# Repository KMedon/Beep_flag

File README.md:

# Football Referee Flags with LoRa Communication
# Overview
This repository houses my engineering project, a cutting-edge set of football referee flags designed with LoRa technology for seamless and effective wireless communication. Aimed at transforming the communication dynamics for referees, especially in lower leagues where advanced communication tools may not be readily available, this project seeks to enhance decision-making accuracy and efficiency on the field.

# Genesis
The inspiration behind this project was to bridge the communication gap faced by referees in lower-tier football leagues. These leagues often lack the resources for sophisticated communication devices, impacting the referees' ability to make quick and accurate decisions. By developing a reliable and easy-to-use set of referee flags with a receiver, this project aims to provide a cost-effective solution that elevates the quality of game officiating across all levels of play.

# Technology
Utilizing LoRa (Long Range) technology at the 868 MHz frequency enables dependable wireless communication over considerable distances. The core of this system is the RAK3172 module, powered by an STM32WLE5 microcontroller, chosen for its performance and reliability. The project was developed in STM32CubeIDE, incorporating the Sub-GHz PHY library for managing wireless communications efficiently.

# Mechanical Design and Testing
The project extends beyond software and communication technologies to include detailed mechanical design and rigorous testing. Files outlining the mechanical construction and assembly of both the flags and the receiver are provided, alongside results from tests designed to evaluate current consumption and the communication range, ensuring system efficiency and field readiness.

# PCB Design
A pivotal aspect of the project is the meticulously designed PCBs for the flag and receiver units. These designs prioritize low power consumption and effective LoRa communication, with durability and component reliability being key considerations to withstand the physical demands of football matches.

# Software
A standout feature of the software is the intuitive interaction between the referee flags and the receiver. When a referee presses the button on a flag, it triggers a buzzer on the receiver unit. This immediate audio feedback ensures that messages are conveyed promptly and unmistakably, supporting referees in maintaining focus on the game without distractions.

The software is crafted with attention to efficiency and responsiveness, ensuring seamless communication between devices. 

# Features
Long-range LoRa communication (868 MHz) tailored for referees in lower leagues
Custom PCB designs for flag and receiver, emphasizing efficiency and durability
In-depth mechanical designs with extensive durability and performance testing
Immediate audio feedback via receiver buzzer upon flag button press
Developed in STM32CubeIDE using the Sub-GHz PHY library

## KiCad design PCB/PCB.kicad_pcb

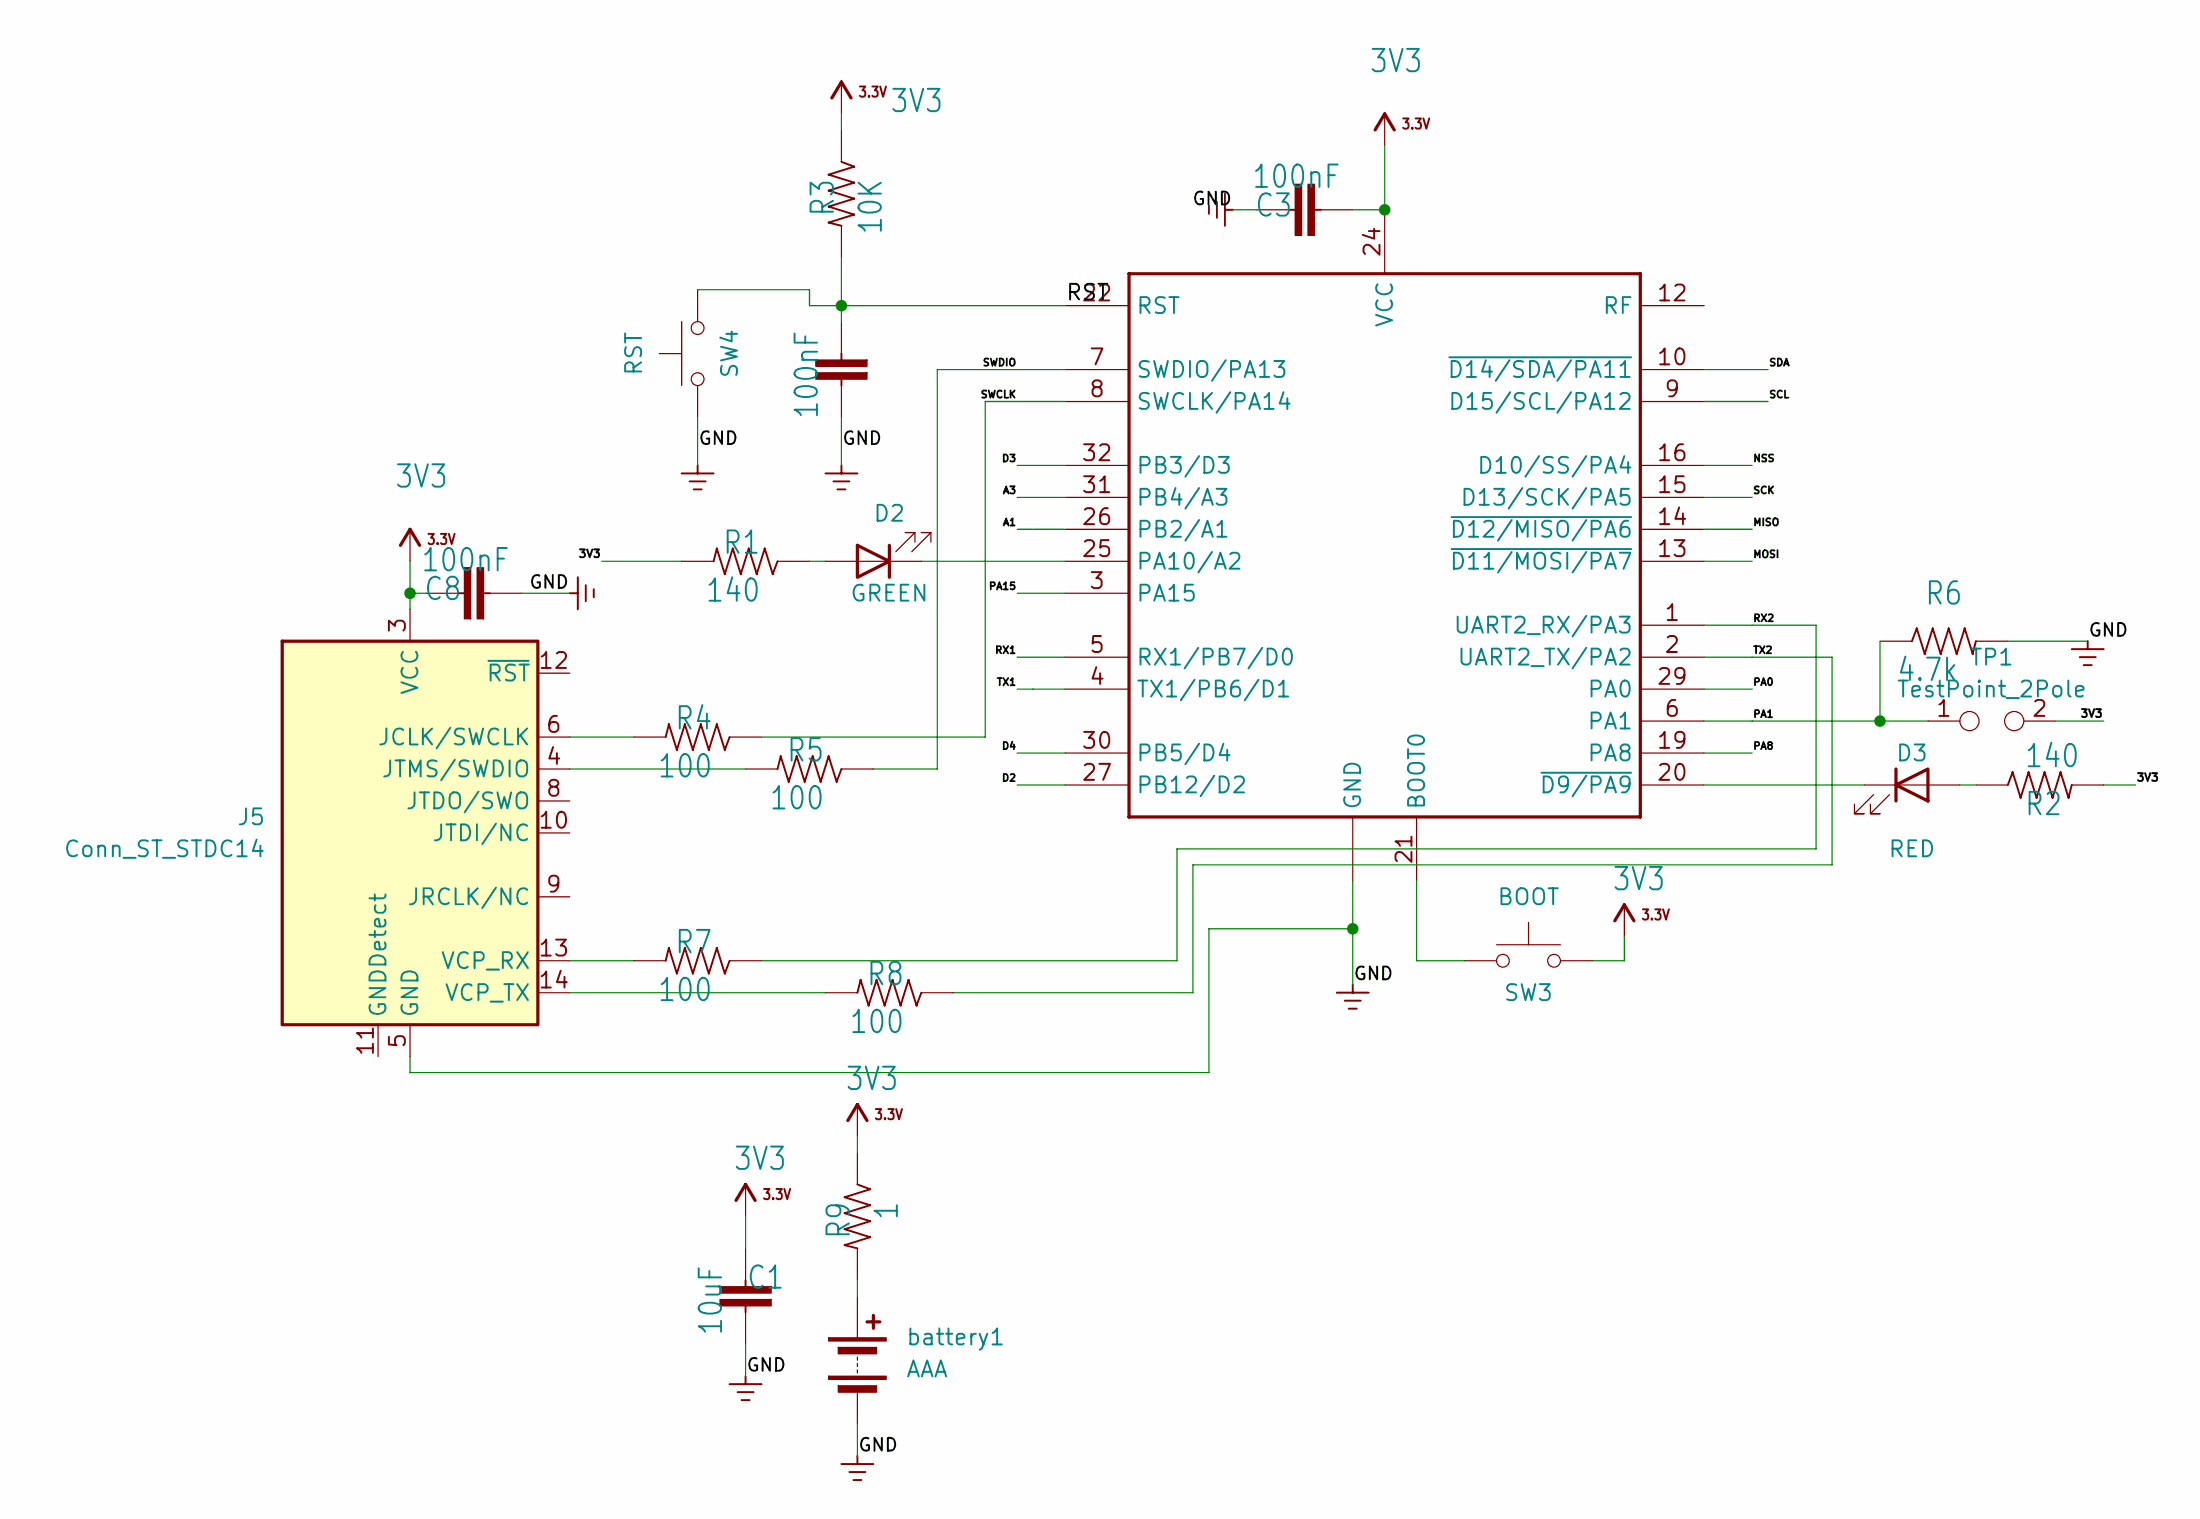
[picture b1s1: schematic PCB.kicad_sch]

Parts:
C1: 10uF; C_0603_1608Metric_Pad1.08x0.95mm_HandSolder
C2, C3, C8: 100nF; C_0603_1608Metric_Pad1.08x0.95mm_HandSolder
D2: GREEN; D_0603_1608Metric_Pad1.05x0.95mm_HandSolder
D3: RED; D_0603_1608Metric_Pad1.05x0.95mm_HandSolder
J5: Conn_ST_STDC14; PinHeader_2x07_P1.27mm_Vertical_SMD
R1, R2: 140; R_0603_1608Metric_Pad0.98x0.95mm_HandSolder
R3: 10K; R_0603_1608Metric_Pad0.98x0.95mm_HandSolder
R4, R5, R7, R8: 100; R_0603_1608Metric_Pad0.98x0.95mm_HandSolder
R6: 4.7k; R_0603_1608Metric_Pad0.98x0.95mm_HandSolder
R9: 1; R_0603_1608Metric_Pad0.98x0.95mm_HandSolder
SW3: BOOT; SW_SPST_B3U-1000P
SW4: RST; SW_SPST_B3U-1000P
TP1: TestPoint_2Pole; TestPoint_2Pads_Pitch2.54mm_Drill0.8mm
U$3: RAK3172HF; 3drak
battery1: AAA; PinHeader_1x02_P2.54mm_Vertical

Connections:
3V3: C1.2, C3.2, C8.1, J5.3 (VCC), R1.2, R2.2, R3.1, R9.1, SW3.2, TP1.2, U$3.24 (VCC)
/A1: U$3.26 (PB2/A1)
/A3: U$3.31 (PB4/A3)
/D2: U$3.27 (PB12/D2)
/D3: U$3.32 (PB3/D3)
/D4: U$3.30 (PB5/D4)
/MISO: U$3.14 (~D12/MISO/PA6)
/MOSI: U$3.13 (~D11/MOSI/PA7)
/NSS: U$3.16 (D10/SS/PA4)
/PA0: U$3.29 (PA0)
/PA1: R6.1, TP1.1, U$3.6 (PA1)
/PA8: U$3.19 (PA8)
/PA15: U$3.3 (PA15)
/RST: C2.2, R3.2, SW4.2, U$3.22 (RST)
/RX1: U$3.5 (RX1/PB7/D0~)
/RX2: R7.1, U$3.1 (UART2_RX/PA3)
/SCK: U$3.15 (D13/SCK/PA5)
/SCL: U$3.9 (D15/SCL/PA12)
/SDA: U$3.10 (~D14/SDA/PA11)
/SWCLK: R4.1, U$3.8 (SWCLK/PA14)
/SWDIO: R5.1, U$3.7 (SWDIO/PA13)
/TX1: U$3.4 (TX1/PB6/D1~)
/TX2: R8.1, U$3.2 (UART2_TX/PA2)
GND: C1.1, C2.1, C3.1, C8.2, J5.5 (GND), J5.7 (GND), R6.2, SW4.1, U$3.11 (GND), U$3.17 (GND), U$3.18 (GND), U$3.23 (GND), U$3.28 (GND), battery1.2 (-)
unnamed: D2.2 (A), R1.1
unnamed: D2.1 (K), U$3.25 (PA10/A2~)
unnamed: D3.2 (A), R2.1
unnamed: D3.1 (K), U$3.20 (~D9/PA9)
unnamed: J5.6 (JCLK/SWCLK), R4.2
unnamed: J5.4 (JTMS/SWDIO), R5.2
unnamed: J5.13 (VCP_RX), R7.2
unnamed: J5.14 (VCP_TX), R8.2
unnamed: SW3.1, U$3.21 (BOOT0)
unnamed: R9.2, battery1.1 (+)

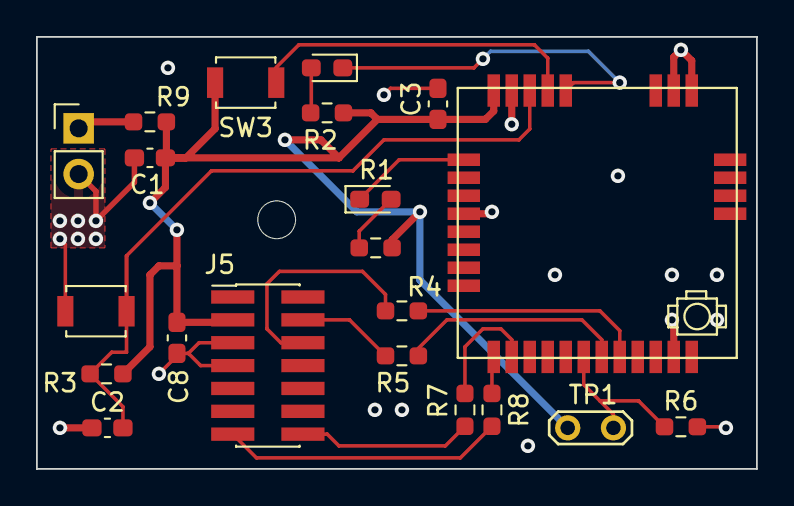
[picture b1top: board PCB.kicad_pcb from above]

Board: 2 copper layers, 40.0 x 24.0 mm, 21 parts (0 on the bottom side), 18 nets.

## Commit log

2023-12-16 Project
    Commit
2023-12-16 Poprawka
2023-12-22 Zmiany
2023-12-22 zmiany2
2023-12-22 Nadajnik
2024-02-05 Add files via upload
    Praca inżynierska PDF
